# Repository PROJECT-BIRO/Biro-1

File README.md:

# Biro-1
A custom media controller for computers, allowing you to easily change volume, play/pause, skip/rewind, and launch favourite applications. Currently being developed!

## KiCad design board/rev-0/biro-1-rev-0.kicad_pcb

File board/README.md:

# Printed Circuit Board
Biro-1 schematics and PCB design files

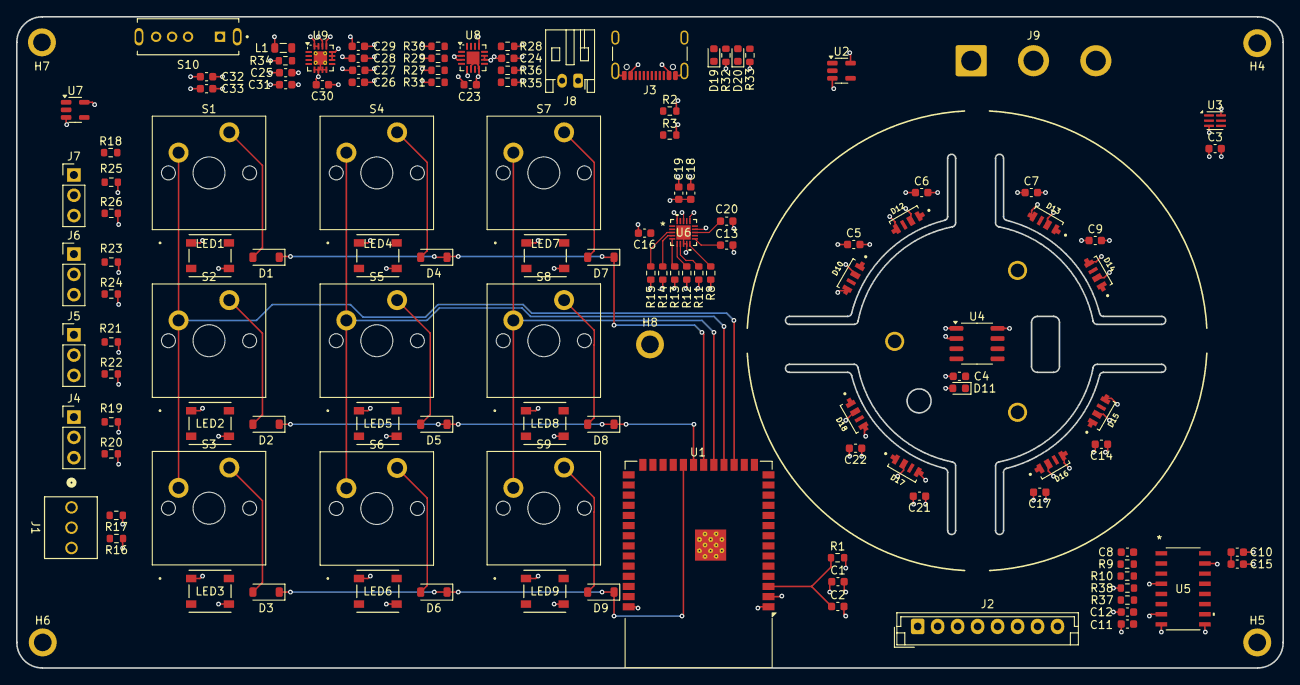
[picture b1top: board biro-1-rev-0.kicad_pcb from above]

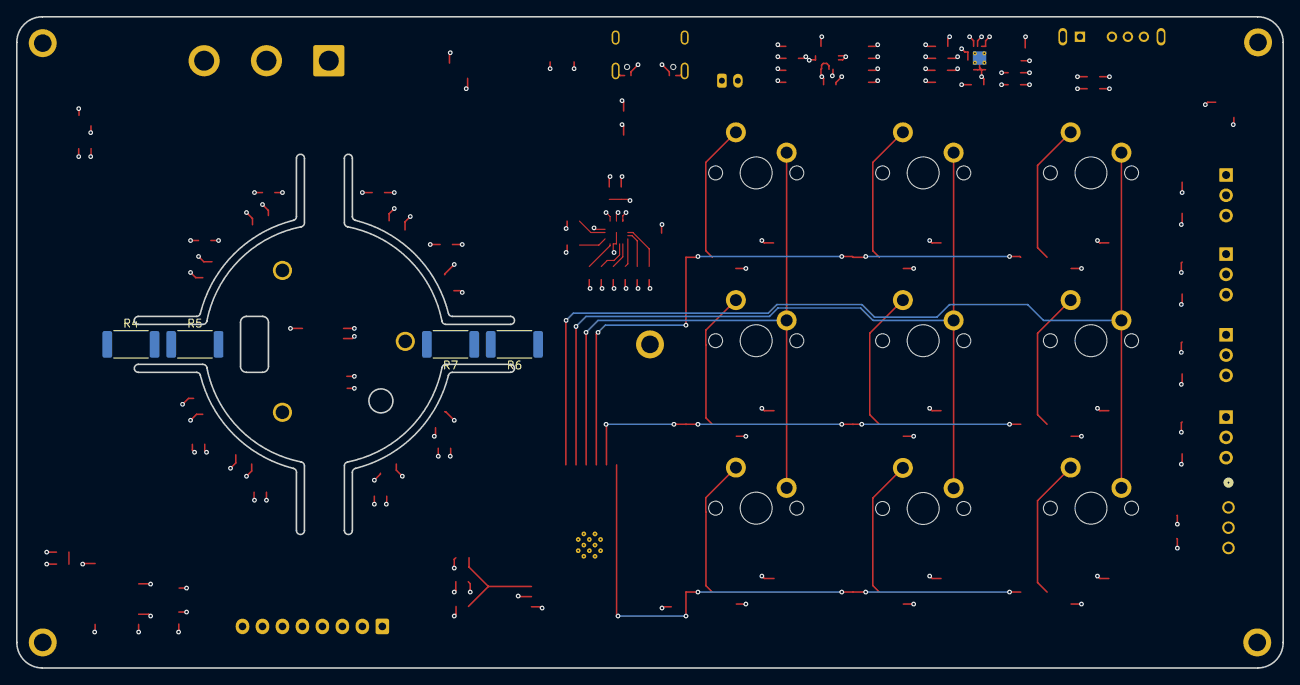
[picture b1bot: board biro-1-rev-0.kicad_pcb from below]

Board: 4 copper layers, 158.5 x 81.5 mm, 137 parts (4 on the bottom side), 100 nets.

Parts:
C1, C19, C28, C32: 10uF; C_0603_1608Metric
C2, C3, C15: 1uF; C_0603_1608Metric
C4, C5, C6, C7, C8, C9, C10, C11, C12, C14, C17, C21, C22, C27, C33: 0.1uF; C_0603_1608Metric
C13: 100nF; C_0603_1608Metric
C16, C18, C20: 10nF; C_0603_1608Metric
C23, C24, C29, C31: 4.7uF; C_0603_1608Metric
C25, C30: 22uF; C_0603_1608Metric
C26: 3.3nF; C_0603_1608Metric
D1, D2, D3, D4, D5, D6, D7, D8, D9: 1N4148W; D_SOD-123
D10, D12, D13, D14, D15, D16, D17, D18: 4691; LED_4691
D11: D_TVS; D_0603_1608Metric
D19, D20: LED; LED_0603_1608Metric
H1, H2, H3: MotorHole; MountingHole_M1.6
H4, H5, H6, H7, H8: ScrewHole; MountingHole_2.2mm_M2_ISO7380_Pad
J1: I2C; CONN_A-6373-03A_MOL
J2: Conn_01x08; JST_EH_B8B-EH-A_1x08_P2.50mm_Vertical
J3: USB_C_Receptacle_USB2.0_16P; USB_C_Receptacle_GCT_USB4105-xx-A_16P_TopMnt_Horizontal
J4, J5, J6, J7: Conn_01x03; PinHeader_1x03_P2.54mm_Vertical
J8: S2B-PH-K-SLFSN; JST_PH_S2B-PH-K_1x02_P2.00mm_Horizontal
J9: Conn_01x03; SolderWire-2sqmm_1x03_P7.8mm_D2mm_OD3.9mm
L1: 2.2uH; L_0805_2012Metric
LED1, LED2, LED3, LED4, LED5, LED6, LED7, LED8, LED9: IN-PI55TATPRPGPB; LED_IN-PI55TAT_INL
R1, R16, R17, R19, R20, R21, R22, R23, R24, R25, R26, R27, R30, R31: 10K; R_0603_1608Metric
R2, R3: 5.1K; R_0603_1608Metric
R4, R5, R6, R7: 330; R_2512_6332Metric
R8, R11, R12, R13, R14, R15, R34, R35, R36, R37: 100K; R_0603_1608Metric
R9, R10: 47; R_0603_1608Metric
R18: 500; R_0603_1608Metric
R28: 1.1K; R_0603_1608Metric
R29: 1.13K; R_0603_1608Metric
R32, R33: 1.5K; R_0603_1608Metric
R38: 50K; R_0603_1608Metric
S1, S2, S3, S4, S5, S6, S7, S8, S9: Keyswitch; MX_PCB_1.00u
S10: SLW-1274547-4A-RA-D; SW_SLW-1274547-4A-RA-D
U1: ESP32-S3-WROOM-1
U2, U7: SN74LV1T34DBV; SOT-23-5
U3: APDS-9306-065; Broadcom_DFN-6_2x2mm_P0.65mm
U4: MT6701CT; SO-8_3.9x4.9mm_P1.27mm
U5: NAU7802SGI; SOI16_NAU7802SGI_NUV
U6: TMC6300-LA-T; 21-100586_K2033&plus_1C_ADI
U8: BQ24075RGT; VQFN-16-1EP_3x3mm_P0.5mm_EP1.6x1.6mm
U9: TPS62132; VQFN-16-1EP_3x3mm_P0.5mm_EP1.68x1.68mm_ThermalVias

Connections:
/Dial/DIAL_LED_DATA_5V: D10.1 (DIN), U2.4 (Y)
/Dial/SCL: U3.1 (SCL), U4.7 (B), U5.13 (SCLK)
/Dial/SDA: U3.2 (SDA), U4.6 (A), U5.14 (SDIO)
/Dial/U: J9.3, U6.15 (U)
/Dial/UH: R15.1, U6.3 (UH)
/Dial/UL: R12.1, U6.6 (UL)
/Dial/V: J9.2, U6.17 (V)
/Dial/VH: R14.1, U6.4 (VH)
/Dial/VIO: C13.1, U6.11 (VIO/NSTDBY)
/Dial/VL: R8.1, U6.10 (VL)
/Dial/W: J9.1, U6.1 (W)
/Dial/WH: R13.1, U6.5 (WH)
/Dial/WL: R11.1, U6.7 (WL)
/MCU/COL_0: S1.1, S2.1, S3.1, U1.17 (IO9)
/MCU/COL_1: S4.1, S5.1, S6.1, U1.18 (IO10)
/MCU/COL_2: S7.1, S8.1, S9.1, U1.19 (IO11)
/MCU/KEY_LED_DATA: J7.2, U1.15 (IO3), U7.2 (A)
/MCU/LCD_BL: J2.6, U1.10 (IO17)
/MCU/LCD_CMD: J2.8, U1.12 (IO8)
/MCU/LCD_CS: J2.7, U1.11 (IO18)
/MCU/LCD_DATA: J2.5, U1.9 (IO16)
/MCU/LCD_RST: J2.3, U1.7 (IO7)
/MCU/LCD_SCK: J2.4, U1.8 (IO15)
/MCU/ROW_0: D1.1 (K), D4.1 (K), D7.1 (K), U1.20 (IO12)
/MCU/ROW_1: D2.1 (K), D5.1 (K), D8.1 (K), U1.21 (IO13)
/MCU/ROW_2: D3.1 (K), D6.1 (K), D9.1 (K), U1.22 (IO14)
/MCU/SCL: J1.3, R16.2, U1.38 (IO2)
/MCU/SDA: J1.2, R17.2, U1.39 (IO1)
/MCU/SW_BT: S10.4, U1.4 (IO4)
/MCU/SW_USB: S10.2, U1.5 (IO5)
/MCU/UH: J5.2, U1.16 (IO46)
/MCU/USB_D+: J3.A6 (D+), J3.B6 (D+), U1.14 (USB_D+)
/MCU/USB_D-: J3.A7 (D-), J3.B7 (D-), U1.13 (USB_D-)
/MCU/VH: J4.2, U1.26 (IO45)
/Power/NCE: R31.1, U8.4 (~CE)
/Power/NCHG: D20.1 (K), R36.2, U8.9 (~CHG)
/Power/NPGOOD: D19.1 (K), R35.2, U8.7 (~PGOOD)
AMB_INT: J6.2, U1.27 (IO0), U3.4 (INT)
BAT+: C23.1, J8.2, R37.1, U8.2 (BAT), U8.3 (BAT)
DIAL_LED_DATA: U1.25 (IO48), U2.2 (A)
GND: C1.2, C2.2, C3.2, C4.2, C5.2, C6.2, C7.2, C9.2, C10.2, C11.2, C12.2, C13.2, C14.2, C15.2, C17.2, C18.2, C19.2, C20.1, C21.2, C22.2, C23.2, C24.2, C25.2, C26.2, C27.2, C28.2, C29.2, C30.2, C31.2, C32.2, C33.2, D10.4 (GND), D11.1 (A1), D12.4 (GND), D13.4 (GND), D14.4 (GND), D15.4 (GND), D16.4 (GND), D17.4 (GND), D18.4 (GND), H1.1, H2.1, H3.1, H4.1, H5.1, H6.1, H7.1, H8.1, J1.1, J2.2, J3.A1 (GND), J3.A12 (GND), J3.B1 (GND), J3.B12 (GND), J3.S1 (SHIELD), J8.1, LED1.1 (GND), LED2.1 (GND), LED3.1 (GND), LED4.1 (GND), LED5.1 (GND), LED6.1 (GND), LED7.1 (GND), LED8.1 (GND), LED9.1 (GND), R2.2, R3.2, R5.2, R7.2, R8.2, R11.2, R12.2, R13.2, R14.2, R15.2, R20.2, R22.2, R24.2, R26.2, R27.2, R28.2, R29.2, R30.2, R31.2, R38.2, U1.1 (GND), U1.40 (GND), U1.41 (GND), U2.3 (GND), U3.6 (GND), U4.4 (GND), U5.4 (VIN2N), U5.7 (REFN), U5.8 (AVSS), U5.9 (DVSS), U6.8 (GND), U6.9 (GND), U6.14 (GND), U6.16 (BRUV), U6.20 (BRW), U6.21 (GND), U7.3 (GND), U8.6 (EN1), U8.8 (VSS), U8.17 (VSS), U9.5 (FB), U9.6 (GND), U9.7 (FSW), U9.8 (DEF), U9.15 (GND), U9.16 (GND), U9.17 (GND)
unnamed: D1.2 (A), S1.2
unnamed: D2.2 (A), S2.2
unnamed: D3.2 (A), S3.2
unnamed: D4.2 (A), S4.2
unnamed: D5.2 (A), S5.2
unnamed: D6.2 (A), S6.2
unnamed: D7.2 (A), S7.2
unnamed: D8.2 (A), S8.2
unnamed: D9.2 (A), S9.2
unnamed: D10.3 (DOUT), D12.1 (DIN)
unnamed: D12.3 (DOUT), D13.1 (DIN)
unnamed: D13.3 (DOUT), D14.1 (DIN)
unnamed: D14.3 (DOUT), D15.1 (DIN)
unnamed: D15.3 (DOUT), D16.1 (DIN)
unnamed: D16.3 (DOUT), D17.1 (DIN)
unnamed: D17.3 (DOUT), D18.1 (DIN)
unnamed: D19.2 (A), R32.2
unnamed: D20.2 (A), R33.2
unnamed: J3.A5 (CC1), R3.1
unnamed: J3.B5 (CC2), R2.1
unnamed: J4.1, R19.2
unnamed: J4.3, R20.1
unnamed: J5.1, R21.2
unnamed: J5.3, R22.1
unnamed: J6.1, R23.2
unnamed: J6.3, R24.1
unnamed: J7.1, R25.2
unnamed: J7.3, R26.1
unnamed: L1.1, U9.1 (SW), U9.2 (SW), U9.3 (SW)
unnamed: LED1.3 (DIN), R18.2
unnamed: LED1.2 (DOUT), LED2.3 (DIN)
unnamed: LED2.2 (DOUT), LED3.3 (DIN)
unnamed: LED3.2 (DOUT), LED4.3 (DIN)
unnamed: LED4.2 (DOUT), LED5.3 (DIN)
unnamed: LED5.2 (DOUT), LED6.3 (DIN)
unnamed: LED6.2 (DOUT), LED7.3 (DIN)
unnamed: LED7.2 (DOUT), LED8.3 (DIN)
unnamed: LED8.2 (DOUT), LED9.3 (DIN)
unnamed: R6.2, R7.1, R9.1
unnamed: R4.2, R5.1, R10.1
unnamed: C2.1, R1.1, U1.3 (EN)
unnamed: C10.1, C15.1, R4.1, R6.1, U5.1 (REFP), U5.16 (AVDD/LDO)
unnamed: C12.1, U5.6 (VBG)
unnamed: C8.1, R9.2, U5.2 (VIN1N)
unnamed: C8.2, R10.2, U5.3 (VIN1P)
unnamed: C11.1, R37.2, R38.1, U5.5 (VIN2P)
unnamed: C20.2, U6.13 (1.8VOUT)
unnamed: C16.1, U6.2 (VCP)
unnamed: R18.1, U7.4 (Y)
unnamed: R28.1, U8.12 (ILIM)
unnamed: R29.1, U8.16 (ISET)
unnamed: R27.1, U8.1 (TS)
unnamed: R34.2, U9.4 (PG)
unnamed: C26.1, U9.9 (SS/TR)
STRAIN_DRDY: U1.24 (IO47), U5.12 (DRDY)
SW_OFF: R30.1, S10.3, U8.15 (SYSOFF)
VCC_3V3: C1.1, C3.1, C4.1, C25.1, C31.1, C32.1, C33.1, D11.2 (A2), J2.1, L1.2, R1.2, R16.1, R17.1, R19.1, R21.1, R23.1, R25.1, R34.1, S10.1, U1.2 (3V3), U3.3 (VDD), U4.1 (VDD), U4.2 (MODE), U4.8 (Z), U5.15 (DVDD), U9.14 (VOS)
VCC_5V5: C5.1, C6.1, C7.1, C9.1, C14.1, C16.2, C17.1, C18.1, C19.1, C21.1, C22.1, C24.1, C27.1, C28.1, C29.1, C30.1, D10.2 (VDD), D12.2 (VDD), D13.2 (VDD), D14.2 (VDD), D15.2 (VDD), D16.2 (VDD), D17.2 (VDD), D18.2 (VDD), LED1.4 (VDD), LED2.4 (VDD), LED3.4 (VDD), LED4.4 (VDD), LED5.4 (VDD), LED6.4 (VDD), LED7.4 (VDD), LED8.4 (VDD), LED9.4 (VDD), R32.1, R33.1, R35.1, R36.1, U2.5 (VCC), U6.18 (VS), U7.5 (VCC), U8.5 (EN2), U8.10 (OUT), U8.11 (OUT), U9.10 (VIN), U9.11 (VIN), U9.12 (VIN), U9.13 (EN)
VIN_5V: J3.A4 (VBUS), J3.A9 (VBUS), J3.B4 (VBUS), J3.B9 (VBUS), U8.13 (IN)

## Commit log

2025-02-12 Created folder structure.
2025-02-12 Updated READMEs
2025-03-02 Added biro project 1 with normalized endings to LF
2025-03-02 Created new branch kevin/initial_fw to start testing
2025-03-08 Testing push on branch
2025-03-16 Deleted old fimrware project files
2025-03-16 Added dial code over to our project
2025-03-16 Updated platformio.ini file to change to our board
2025-03-21 Added Adafruit TinyUSB and NimBLE Libraries to platformio.ini
2025-03-23 added battery schematic
2025-03-28 Initial kicad files for Rev 0 schematic
2025-03-28 Removed stale files
2025-03-28 Added lib
2025-03-28 Added pdf
2025-03-29 disable hardware
2025-04-06 Changed PSRAM pins
2025-04-06 Updated TMC6300 VIO cap to 100nF
2025-04-06 Added I2C pullups and LCD net labels
2025-04-06 Added key LEDs
2025-04-13 Added strapping GPIO pull-up/-down options, replaced UART breakout with charging status signals
2025-04-13 Updated pdf
2025-04-20 Added power circuitry
2025-04-26 First crack at layout, added scottokeebs 3d files
2025-04-27 program works
2025-05-02 Serial Monitoring Fixed (#17)
    * disable hardware
    * program works
    ---------
2025-05-14 Added battery divider to ADC, created board step file, updated to kicad 9
2025-05-15 bt task
2025-05-16 bluetooth connection established
2025-09-02 Added mounting holes, minor schematic fixes, layout progress
2025-09-03 Schematic Rev 0 (#15)
    * Initial kicad files for Rev 0 schematic
    * Removed stale files
    * Added lib
    * Added pdf
    * Changed PSRAM pins
    * Updated TMC6300 VIO cap to 100nF
